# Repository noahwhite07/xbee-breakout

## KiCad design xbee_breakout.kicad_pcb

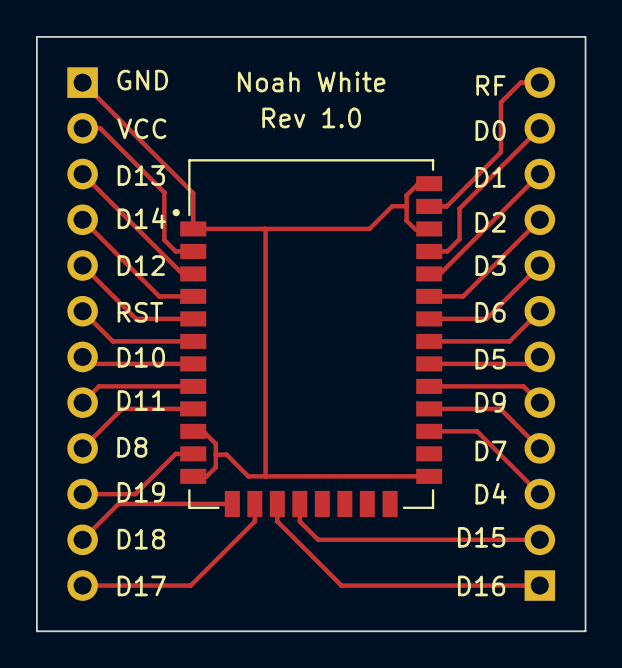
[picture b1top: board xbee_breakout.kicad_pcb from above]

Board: 2 copper layers, 30.5 x 33.0 mm, 3 parts (0 on the bottom side), 24 nets.

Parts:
J1, J2: Conn_01x12_Female; PinHeader_1x12_P2.54mm_Vertical
U1: XB3-24Z8CM-J; XB3-24Z8UM-J

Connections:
D0: J2.11, U1.31 (AD0/DIO0)
D1: J2.10, U1.30 (AD1/DIO1)
D2: J2.9, U1.29 (AD2/DIO2)
D3: J2.8, U1.28 (AD3/DIO3)
D4: J2.3, U1.23 (DIO4)
D5: J2.6, U1.26 (ASSOCIATE/DIO5)
D6: J2.7, U1.27 (~RTS~{/DIO6)
D7: J2.4, U1.24 (~CTS~{/DIO7)
D8: J1.9, U1.9 (~DTR~{/SLEEP_RQ/DIO8)
D9: J2.5, U1.25 (ON/~SLEEP~{/DIO9)
D10: J1.7, U1.7 (RSSI_PWM/DIO10)
D11: J1.8, U1.8 (PWM1/DIO11)
D12: J1.5, U1.5 (DIO12)
D13: J1.3, U1.3 (DOUT/DIO13)
D14: J1.4, U1.4 (DIN/~CONFIG~{/DIO14)
D15: J2.2, U1.16 (SPI_MISO/DIO15)
D16: J2.1, U1.15 (SPI_MOSI/DIO16)
D17: J1.12, U1.14 (SPI_~SSEL~{/DIO17)
D18: J1.11, U1.13 (SPI_CLK/DIO18)
D19: J1.10, U1.11 (SPI_~ATTN~{/~{BOOTMODE~{/DIO19)
GND: J1.1, U1.1 (GND), U1.10 (GND), U1.12 (GND), U1.21 (GND), U1.32 (GND), U1.34 (GND)
RF: J2.12, U1.33 (RF)
RST: J1.6, U1.6 (~RESET)
VCC: J1.2, U1.2 (VCC)
